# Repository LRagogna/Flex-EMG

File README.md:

# Flex-EMG

Notion Link: https://tabby-coat-711.notion.site/FlexEMG-110f756f6bd680bfb4d2c9bf16184d59

A wearable surface-electromyography (sEMG) platform that reads muscle activity
from the forearm, cleans it with a real-time digital filter chain, and
classifies hand gestures using a lightweight machine-learning model.

The project spans the full stack: a custom analog front-end (AFE) PCB, ESP32
firmware that streams ADC samples over WiFi, and a Python backend that filters
the signal, recognizes gestures, and broadcasts results to any client over
WebSocket.

> Built by the **Neurotech at Berkeley** Flex-EMG team, Spring 2026.

---

## How it works

```
 Forearm muscles
       │  surface electrodes
       ▼
 Analog Front-End PCB ── instrumentation amp → filtering → 24-bit ADC
       │  digital samples
       ▼
 ESP32-C3 firmware ─────── streams {"v": <adc>} over WiFi / serial
       │
       ▼
 Python backend ────────── bandpass 20–500 Hz + 60 Hz notch
       │                   Hudgins features → LDA gesture classifier
       ▼
 WebSocket broadcast ───── live frames to dashboards / notebooks / viewers
```

Each processed frame is streamed as JSON:

```json
{ "ts": 1713456789.12, "raw": 1.65, "filtered": 0.042, "gesture": "Fist Squeeze", "confidence": 0.97 }
```

---

## Hardware

The custom AFE board conditions a microvolt-level EMG signal into a clean
digital stream:

- **ADS1220** — 24-bit delta-sigma ADC with integrated PGA
- **OPA4322** — quad precision op-amps for the analog filter / gain stages
- **MCP4141** — digital potentiometer for programmable gain
- **ESP32-C3** — onboard wireless MCU for sampling and streaming

KiCad source (schematic, layout, footprints, and BOM) lives in
[`finalKiCad/`](finalKiCad/).

### Gallery

| | |
|:---:|:---:|
| <br>**Breadboard prototype** of the front-end | <br>**Fabricated AFE board** fresh from the fab |
| <br>**Reflow + rework bench** used for assembly | <br>**Applying solder paste to board** |
| <br>**Layout under the scope** during placement | <br>**Soldered ICs** — ADC and op-amp stages |

---

## Software

The backend lives in [`backend/`](backend/) and is fully documented in
[`backend/DOCS.md`](backend/DOCS.md). Key modules:

| Module | Role |
|--------|------|
| `config.py` | Single source of truth for sample rate, filter, and connection settings |
| `signal_processor.py` | Real-time bandpass + 60 Hz notch filter chain (SciPy SOS) |
| `esp32_client.py` | WiFi/serial reader with auto-reconnect |
| `classifier.py` | Hudgins time-domain features → StandardScaler + LDA pipeline |
| `server.py` | WebSocket server that fans frames out to all clients |
| `main.py` | Production entry point (`--train`, `--classify`) |
| `test.py` | Hardware-free simulator with a live viewer and training UI |

---

## Getting started

### 1. Simulation (no hardware required)

```bash
cd backend
pip install -r requirements.txt
python test.py          # live matplotlib viewer
python test.py --text   # terminal table mode
```

Hold `1` / `2` to record the two gesture classes, press `T` to train, then `P`
to toggle live prediction. See [`backend/DOCS.md`](backend/DOCS.md) for the full
key map.

### 2. Real hardware

1. Flash `backend/esp32_firmware/emg_sender.ino` to the ESP32 (edit the WiFi and
   backend host lines first).
2. Point `config.py` at your board:
   ```python
   ESP32_MODE   = "websocket"
   ESP32_WS_URI = "ws://<your-esp32-ip>:81"
   ```
3. Collect data and run live classification:
   ```bash
   python main.py --train      # guided data collection
   python main.py --classify   # stream gestures over ws://0.0.0.0:8765
   ```

---

## Repository layout

```
backend/        Python signal-processing + ML pipeline (see DOCS.md)
finalKiCad/     KiCad project: schematic, PCB layout, footprints, BOM
pics/           Project photos
```

---

## Team

Neurotech at Berkeley — Flex-EMG, Spring 2026:
Alex Wong · Sean Isomatsu · Leo Ragogna · Abhay Bharnidharka · Kabeer Nayyar · Edgar Amazcua

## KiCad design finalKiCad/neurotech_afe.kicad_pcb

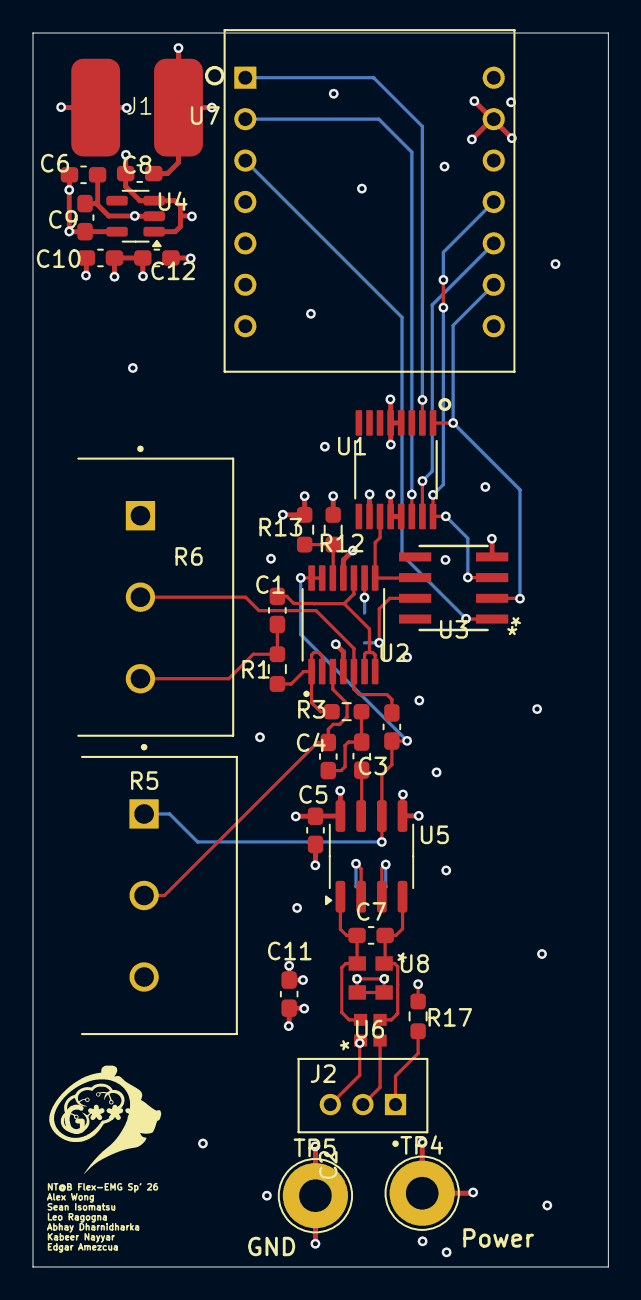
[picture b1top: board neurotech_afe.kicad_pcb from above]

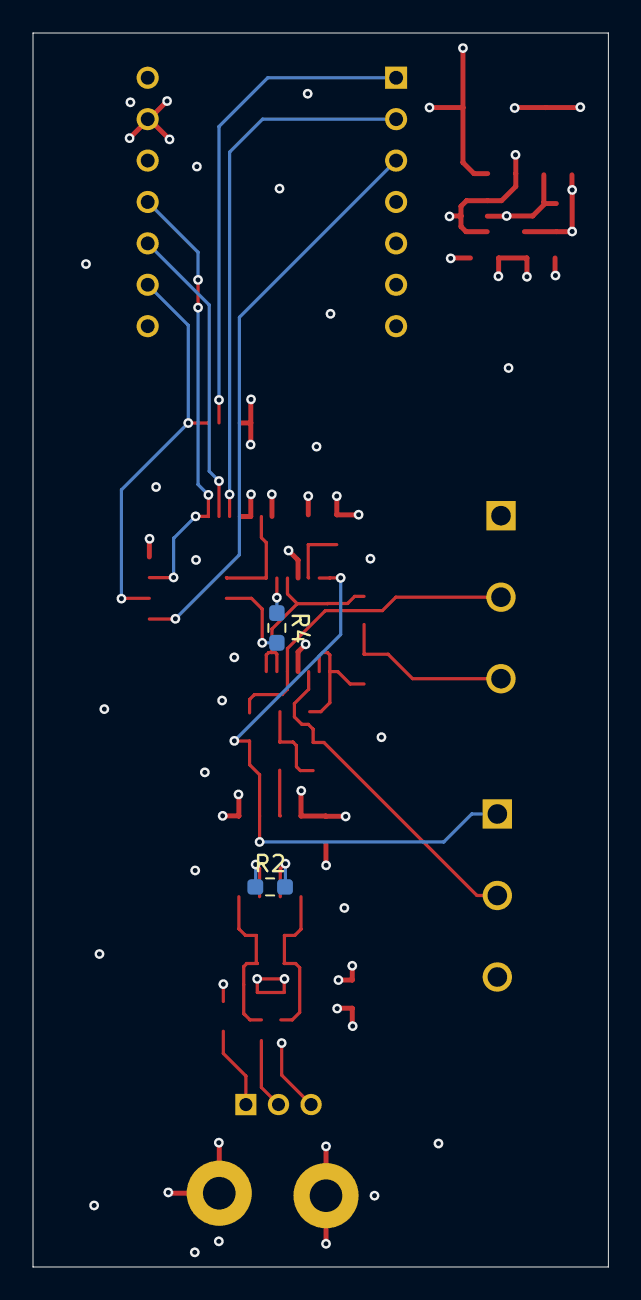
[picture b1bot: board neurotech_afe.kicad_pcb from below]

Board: 4 copper layers, 35.3 x 75.7 mm, 33 parts (2 on the bottom side), 28 nets.

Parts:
C1: 10nF; C_0603_1608Metric_Pad1.08x0.95mm_HandSolder
C2: 22nF; C_0603_1608Metric_Pad1.08x0.95mm_HandSolder
C3: 1uF; C_0603_1608Metric_Pad1.08x0.95mm_HandSolder
C4: 2.2uF; C_0603_1608Metric_Pad1.08x0.95mm_HandSolder
C5: 0.1u; C_0603_1608Metric_Pad1.08x0.95mm_HandSolder
C6: 10u; C_0603_1608Metric_Pad1.08x0.95mm_HandSolder
C7: 4.7n; C_0603_1608Metric_Pad1.08x0.95mm_HandSolder
C8, C9: 1 uF; C_0603_1608Metric_Pad1.08x0.95mm_HandSolder
C10, C11: 0.1 uF; C_0603_1608Metric_Pad1.08x0.95mm_HandSolder
C12: 100nF; C_0603_1608Metric_Pad1.08x0.95mm_HandSolder
J1: Conn_01x02_Pin; BATT_CONN
J2: B3B-PH-K-S; JST_B3B-PH-K-S
R1, R3, R12, R13: 10k; R_0603_1608Metric_Pad0.98x0.95mm_HandSolder
R2: 510; R_0603_1608Metric_Pad0.98x0.95mm_HandSolder
R4: 3.3k; R_0603_1608Metric_Pad0.98x0.95mm_HandSolder
R5: 20k; POT_PTN16-A20120K1B1
R6: 50k; POT_PTN16-A20120K1B1
R17: 100k; R_0603_1608Metric_Pad0.98x0.95mm_HandSolder
TP4, TP5: TestPoint; TestPoint_THTPad_D4.0mm_Drill2.0mm
U1: ADS1220xPW; SOP65P640X120-16N
U2: Opamp_Quad; SOP65P640X120-14N
U3: MCP4141T-103E/SN; SOIC8-N_MC_MCH
U4: TLV70033_SOT23-5; SOT-23-5
U5: AD8226ARZ; SOIC-8_3.9x4.9mm_P1.27mm
U6: EXB24V332JX; C_ARRAY_EXB24V_PAN
U7: 113991054; ESP32C3
U8: EXB34V105JV; C_ARRAY_EXB34V_PAN

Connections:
+3.3V: C5.1, C6.1, C9.1, C10.1, C11.1, C12.1, R12.1, TP4.1, U1.10 (AIN1), U1.12 (AVDD), U1.13 (DVDD), U2.4 (V+), U3.4, U4.5 (OUT), U5.8 (VS+), U7.12 (VCC_3V3)
/1.65 V: C2.2, R5.1, R17.1, U2.13 (-), U2.14, U5.6 (REF), U8.3, U8.4
/3V7: C8.1, J1.1, U4.1 (IN), U4.3 (EN)
/CS: U1.2 (~CS), U7.1 (D0)
/CS1: U3.1, U7.3 (D2)
/DIN: U1.16 (DIN), U3.3, U7.11 (D10)
/DOUT: U1.15 (DOUT/~DRDY), U7.10 (D9)
/DRDY: U1.14 (~DRDY), U7.2 (D1)
/IAout: C3.1, U5.7 (VOUT)
/In+: C7.2, U5.4 (IN+), U6.3, U8.1
/In-: C7.1, U5.1 (IN-), U6.4, U8.2
/Negative_Electrode: J2.3, U6.1
/Positive_Electrode: J2.2, U6.2
/Reference_Electrode: J2.1, R17.2
/SCLK: U1.1 (SCLK), U3.2, U7.9 (D8)
/Vout: U1.11 (AIN0/REFP1), U2.8, U3.6
GND: C5.2, C6.2, C8.2, C9.2, C10.2, C11.2, C12.2, J1.2, R13.2, TP5.1, U1.4 (DGND), U1.5 (AVSS), U2.11 (V-), U4.2 (GND), U5.5 (VS-), U7.13 (GND)
unnamed: C1.1, R1.2, R6.3
unnamed: C3.2, C4.1, R3.1
unnamed: R2.1, U5.3 (RG)
unnamed: R2.2, U5.2 (RG)
unnamed: R4.2, U3.7
unnamed: C4.2, R5.2, U2.3 (+)
unnamed: R1.1, R3.2, U2.1, U2.2 (-)
unnamed: C2.1, R6.2, U2.5 (+)
unnamed: C1.2, U2.6 (-), U2.7, U2.10 (+)
unnamed: R4.1, U2.9 (-)
unnamed: R12.2, R13.1, U2.12 (+)

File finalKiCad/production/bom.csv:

Designator,Footprint,Quantity,Value,LCSC Part #
C1,0603,1,10nF,
"C10, C11",0603,2,0.1 uF,
C12,0603,1,100nF,
C2,0603,1,22nF,
C3,0603,1,1uF,
C4,0603,1,2.2uF,
C5,0603,1,0.1u,
C6,0603,1,10u,
C7,0603,1,4.7n,
"C8, C9",0603,2,1 uF,
J1,BATT_CONN,1,Conn_01x02_Pin,
J2,JST_B3B-PH-K-S,1,B3B-PH-K-S,
"R1, R12, R13, R3",0603,4,10k,
R17,0603,1,100k,
R2,0603,1,510,
R4,0603,1,3.3k,
R5,POT_PTN16-A20120K1B1,1,20k,
R6,POT_PTN16-A20120K1B1,1,50k,
"TP4, TP5",TestPoint_THTPad_D4.0mm_Drill2.0mm,2,TestPoint,
U1,SOP65P640X120-16N,1,ADS1220xPW,
U2,SOP65P640X120-14N,1,Opamp_Quad,
U3,SOIC8-N_MC_MCH,1,MCP4141T-103E/SN,
U4,SOT-23-5,1,TLV70033_SOT23-5,
U5,SOIC-8_3.9x4.9mm_P1.27mm,1,AD8226ARZ,
U6,C_ARRAY_EXB24V_PAN,1,EXB24V332JX,
U7,ESP32C3,1,113991054,
U8,C_ARRAY_EXB34V_PAN,1,EXB34V105JV,

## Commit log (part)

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2026-02-22 Add local FlexEMG files
2026-02-22 remove test.py file
2026-02-22 testing python file added under leo branch
2026-02-22 added project schematic before sallen key implementation
2026-02-22 Sallen Key Implementation added and schtokky diodes added to front part of circuit
2026-03-04 instrumentation amp spice sim
2026-03-07 deleted test file
2026-03-07 spice now works with these files
2026-03-08 created asc file with the circuit's full gain. Does not include any frequency filters
2026-03-08 added digipots
2026-03-08 added sallen key topology to circuit 20-500 HZ
2026-03-08 finished wiring
2026-03-08 digipots
2026-03-10 in progress
2026-03-11 Added LDO voltage stepdown from 3.3 --> 3.7 and basic connections to ADS
2026-03-11 added 3.7 --> 3.3 V LDO
2026-03-13 changed ldo output power rail to 3.3V flag
2026-03-28 added LTSpice Folder
2026-04-05 kabeer's schematic added
2026-04-05 final kiCad pushed to main
2026-04-05 push
2026-04-05 Track only KiCad sources; remove LTSpice prototype files
2026-04-05 only have kiCad files in git
2026-04-05 added final schematic
2026-04-07 combined all 4 op amps to same quad op amp
2026-04-08 fixed ERC errors
2026-04-08 assigned passive footprints
2026-04-08 cleaned up schm
2026-04-09 Created pcb layout and started wiring
2026-04-09 created git ignore
2026-04-09 chore: update gitignore, remove generated files
2026-04-09 chore: untrack generated KiCad files
2026-04-09 chore: gitignore KiCad generated files
2026-04-10 added csv for bom
2026-04-10 reassigned footprints and values
2026-04-12 lotta stuff
2026-04-12 Update schematic, symbols, and footprints
2026-04-17 footprints and started layout
2026-04-18 routing
2026-04-19 Add Python backend: signal filtering, gesture classifier, and simulator
2026-04-19 clauded simulator may be boof
2026-04-20 silkscreen
2026-04-21 final
2026-06-18 Add project README with photos and clean up tracked build artifacts
    - Replace the placeholder README with a project overview, architecture
    diagram, hardware notes, photo gallery, and getting-started guide
    - Add project photos with descriptive filenames
    - Stop tracking __pycache__, KiCad lock/backup files, and a stray
    submodule reference; broaden .gitignore to cover them
